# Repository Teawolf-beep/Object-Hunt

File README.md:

# Object-Hunt
Searches and identifies an object in an unknown environment.

This project was developed in the University of Applied Sciences Cologne due to a research project in the subject "Special Aspects of Mobile Autonomous Systems". 

## Documentation

Please refer to the [documentation page](https://teawolf-beep.github.io/index.html) for all further information regarding the project.

## Repository Structure

The following briefly describes the content of the existing directories.

Directory | Content
---|---
Eagle | Circuit schematics and PCB layout. Drafted with [Autodesk EAGLE](https://www.autodesk.com/products/eagle/overview).
Files_rpi | Configuration files of the Raspberry Pi. The exact path is written in the first line of each file.
Final_presentation | A demonstration video and the slides of the final presentation (presentation_team00.pdf).
FreeCAD | Construction files of 3D printed parts. Drafted with [FreeCAD](https://www.freecadweb.org/).
Kick-off_presentation | The slides of the kick-off presentation.
Proposal | The proposal written at the beginning of this project (proposal_group0.pdf).
Report | The final report (report.pdf).
object_hunt_base | Source code of the base process. Written in C++.
object_hunt_camera | Source code of the camera process. Written in Python.
object_hunt_mapping | Source code of the mapping process. Written in Java.
object_hunt_navigation | Source code of the navigation process. Written in C++.
scripts | Bash scripts to facilitate the usage of external software.

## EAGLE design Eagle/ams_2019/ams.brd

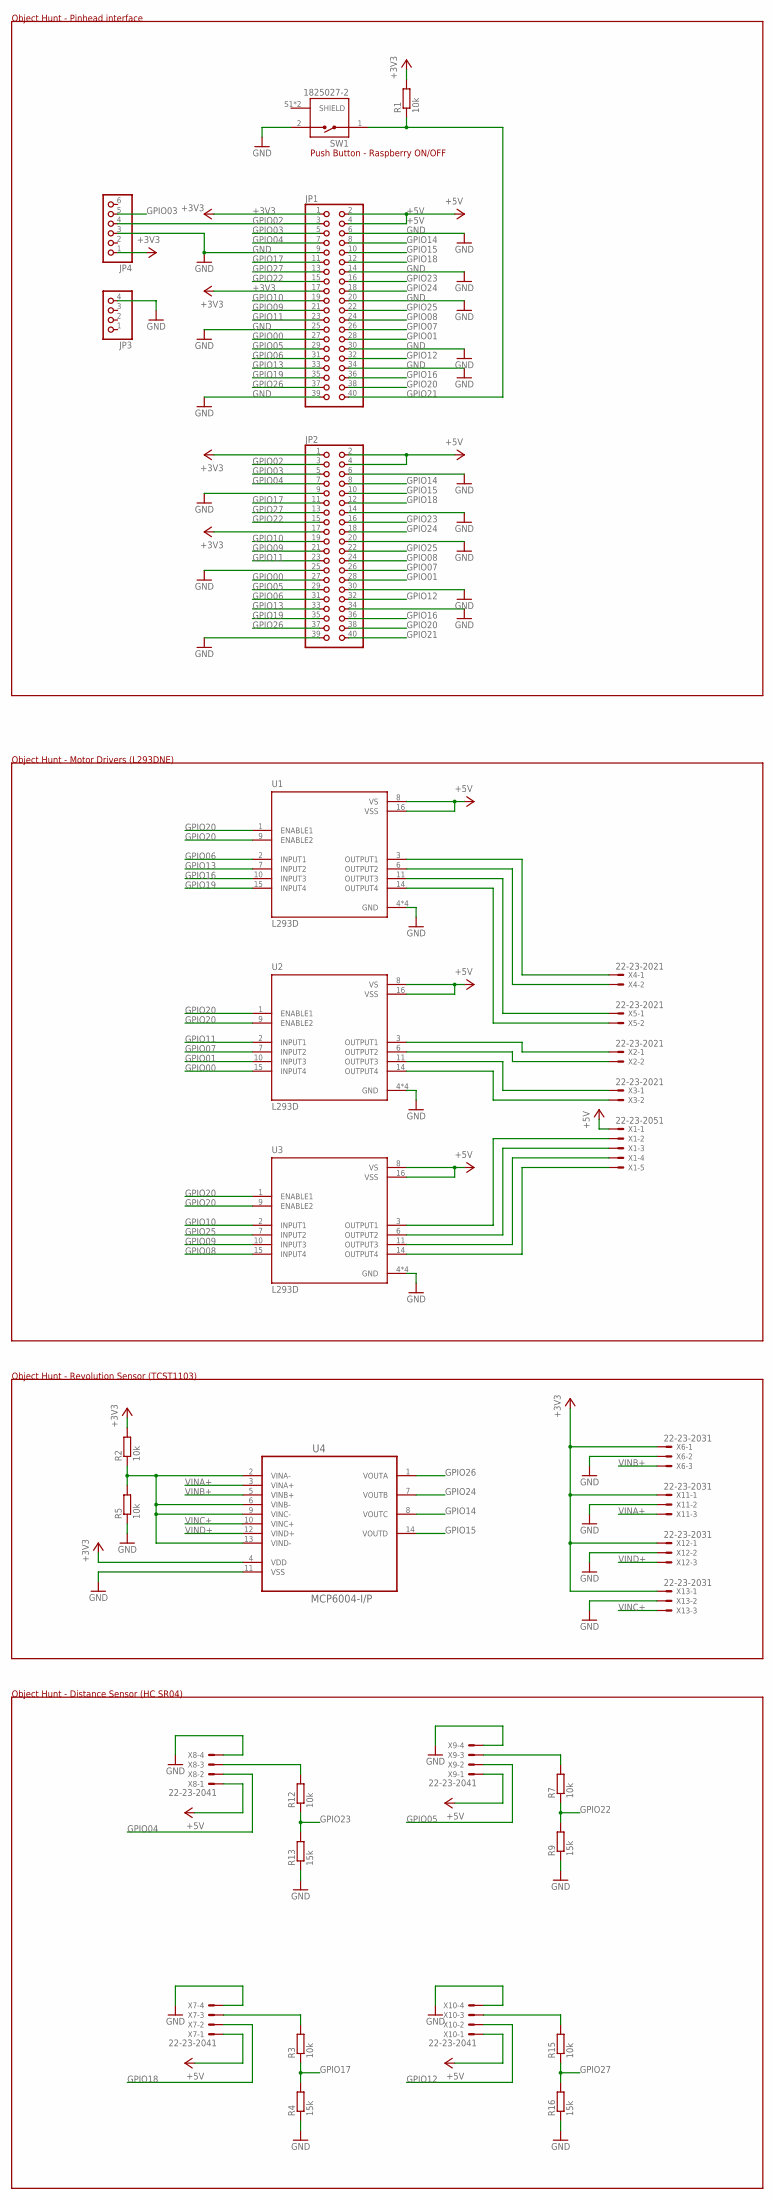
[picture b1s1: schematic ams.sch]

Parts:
JP1, JP2: PINHD-2X20; 2X20
JP3: PINHD-1X4; 1X04
JP4: PINHD-1X6; 1X06
R1, R2, R3, R5, R7, R12, R15: 10k; 0204/7
R4, R9, R13, R16: 15k; 0204/7
SW1: 1825027-2; TE_1825027-2
U1, U2, U3: L293D; DIP880W50P254L2000H510Q16
U4: MCP6004-I/P; DIP254P762X533-14
X1: 22-23-2051
X2, X3, X4, X5: 22-23-2021
X6, X11, X12, X13: 22-23-2031
X7, X8, X9, X10: 22-23-2041

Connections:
+3V3: JP1.1, JP1.17, JP2.1, JP2.17, JP4.1, R1.2, R2.2, U4.4 (VDD), X6.1, X11.1, X12.1, X13.1
+5V: JP1.2, JP1.4, JP2.2, JP2.4, U1.8 (VS), U1.16 (VSS), U2.8 (VS), U2.16 (VSS), U3.8 (VS), U3.16 (VSS), X1.1, X7.1, X8.1, X9.1, X10.1
GND: JP1.6, JP1.9, JP1.14, JP1.20, JP1.25, JP1.30, JP1.34, JP1.39, JP2.6, JP2.9, JP2.14, JP2.20, JP2.25, JP2.30, JP2.34, JP2.39, JP3.4, JP4.3, R4.1, R5.1, R9.1, R13.1, R16.1, SW1.2, U1.4 (GND), U1.5 (GND), U1.12 (GND), U1.13 (GND), U2.4 (GND), U2.5 (GND), U2.12 (GND), U2.13 (GND), U3.4 (GND), U3.5 (GND), U3.12 (GND), U3.13 (GND), U4.11 (VSS), X6.2, X7.4, X8.4, X9.4, X10.4, X11.2, X12.2, X13.2
GPIO00: JP1.27, JP2.27, U2.15 (INPUT4)
GPIO01: JP1.28, JP2.28, U2.10 (INPUT3)
GPIO02: JP1.3, JP2.3, JP4.4
GPIO03: JP1.5, JP2.5, JP4.5
GPIO04: JP1.7, JP2.7, X8.2
GPIO05: JP1.29, JP2.29, X9.2
GPIO06: JP1.31, JP2.31, U1.2 (INPUT1)
GPIO07: JP1.26, JP2.26, U2.7 (INPUT2)
GPIO08: JP1.24, JP2.24, U3.15 (INPUT4)
GPIO09: JP1.21, JP2.21, U3.10 (INPUT3)
GPIO10: JP1.19, JP2.19, U3.2 (INPUT1)
GPIO11: JP1.23, JP2.23, U2.2 (INPUT1)
GPIO12: JP1.32, JP2.32, X10.2
GPIO13: JP1.33, JP2.33, U1.7 (INPUT2)
GPIO14: JP1.8, JP2.8, U4.8 (VOUTC)
GPIO15: JP1.10, JP2.10, U4.14 (VOUTD)
GPIO16: JP1.36, JP2.36, U1.10 (INPUT3)
GPIO17: JP1.11, JP2.11, R3.1, R4.2
GPIO18: JP1.12, JP2.12, X7.2
GPIO19: JP1.35, JP2.35, U1.15 (INPUT4)
GPIO20: JP1.38, JP2.38, U1.1 (ENABLE1), U1.9 (ENABLE2), U2.1 (ENABLE1), U2.9 (ENABLE2), U3.1 (ENABLE1), U3.9 (ENABLE2)
GPIO21: JP1.40, JP2.40, R1.1, SW1.1
GPIO22: JP1.15, JP2.15, R7.1, R9.2
GPIO23: JP1.16, JP2.16, R12.1, R13.2
GPIO24: JP1.18, JP2.18, U4.7 (VOUTB)
GPIO25: JP1.22, JP2.22, U3.7 (INPUT2)
GPIO26: JP1.37, JP2.37, U4.1 (VOUTA)
GPIO27: JP1.13, JP2.13, R15.1, R16.2
unnamed: R3.2, X7.3
unnamed: R2.1, R5.2, U4.2 (VINA-), U4.6 (VINB-), U4.9 (VINC-), U4.13 (VIND-)
unnamed: R7.2, X9.3
unnamed: R15.2, X10.3
unnamed: U1.3 (OUTPUT1), X4.1
unnamed: U1.6 (OUTPUT2), X4.2
unnamed: U1.11 (OUTPUT3), X5.1
unnamed: U1.14 (OUTPUT4), X5.2
unnamed: U2.3 (OUTPUT1), X2.1
unnamed: U2.6 (OUTPUT2), X2.2
unnamed: U2.11 (OUTPUT3), X3.1
unnamed: U2.14 (OUTPUT4), X3.2
unnamed: U3.3 (OUTPUT1), X1.2
unnamed: U3.6 (OUTPUT2), X1.3
unnamed: U3.11 (OUTPUT3), X1.4
unnamed: U3.14 (OUTPUT4), X1.5
unnamed: R12.2, X8.3
VINA+: U4.3 (VINA+), X11.3
VINB+: U4.5 (VINB+), X6.3
VINC+: U4.10 (VINC+), X13.3
VIND+: U4.12 (VIND+), X12.3

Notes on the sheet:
Push Button - Raspberry ON/OFF
Object Hunt - Pinhead interface
Object Hunt - Distance Sensor (HC SR04)
Object Hunt - Revolution Sensor (TCST1103)
Object Hunt - Motor Drivers (L293DNE)

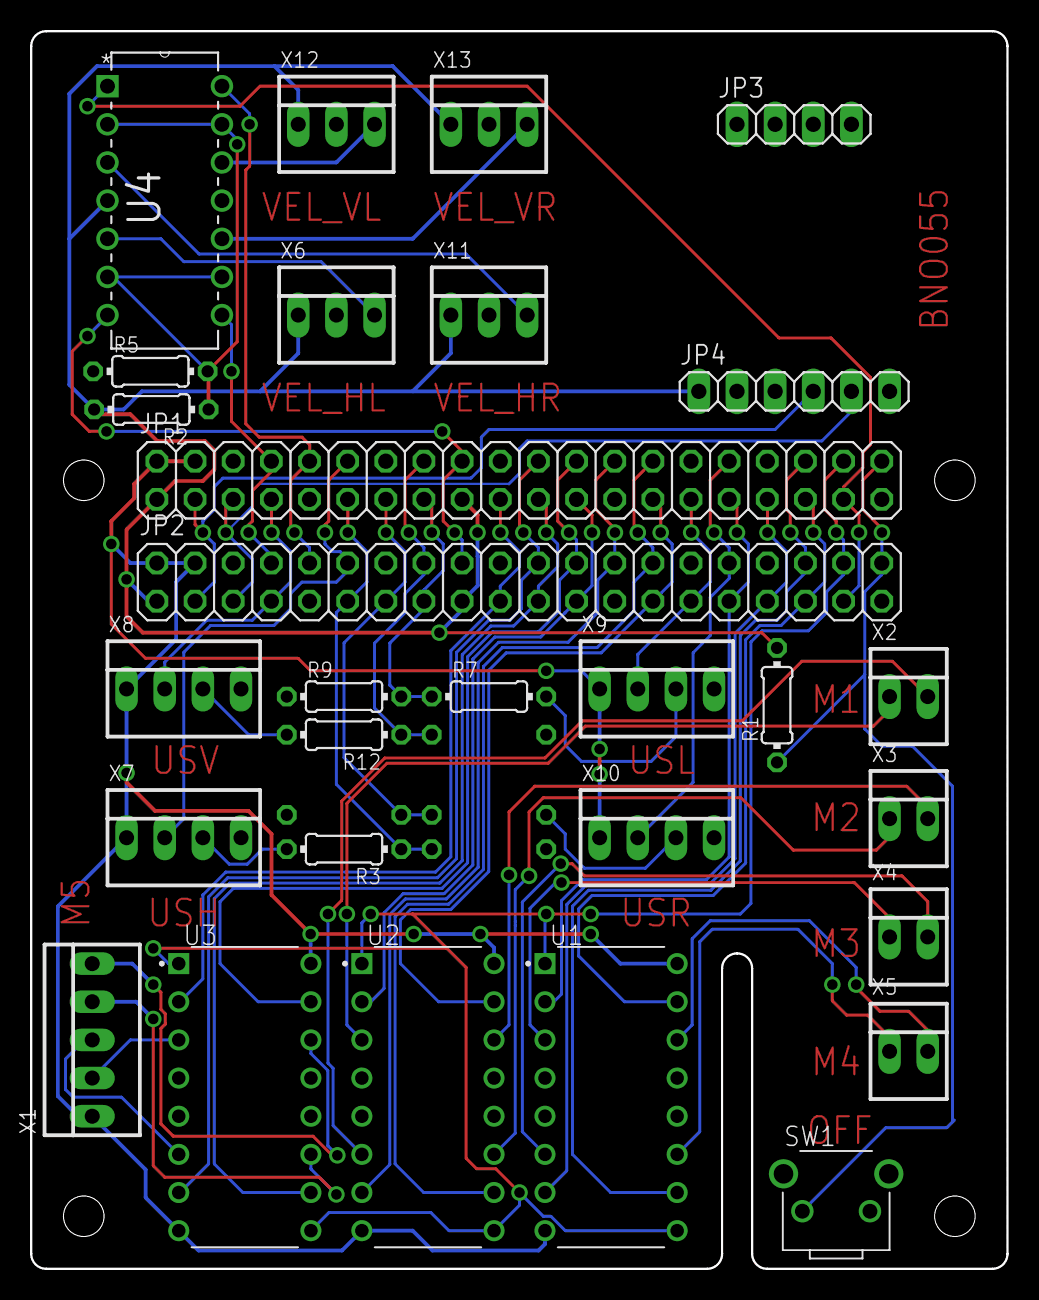
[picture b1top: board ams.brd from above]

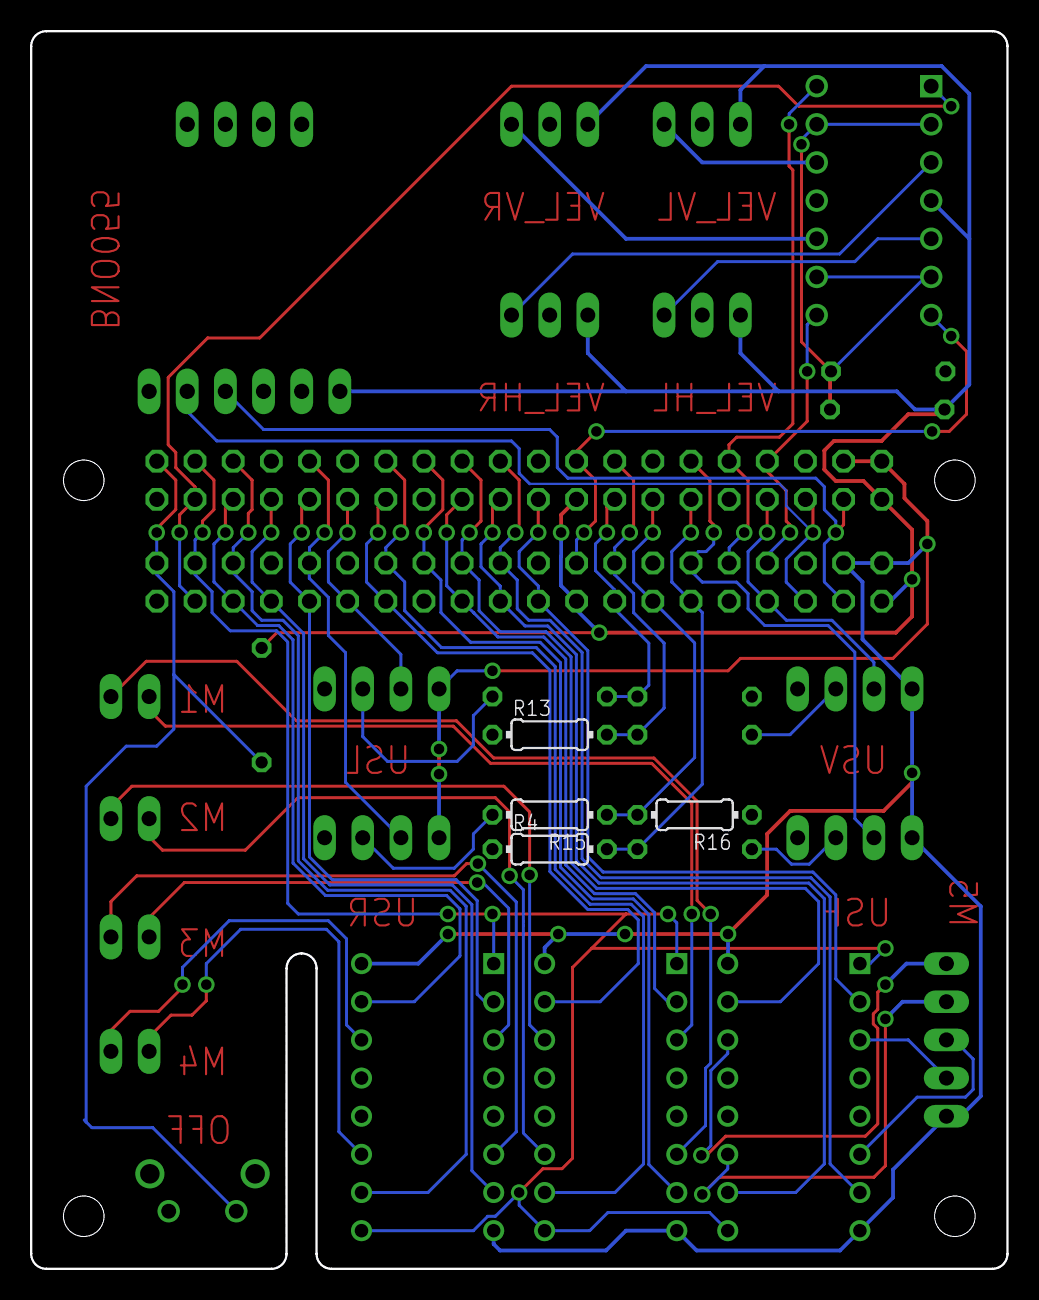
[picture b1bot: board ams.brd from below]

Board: 2 copper layers, 65.0 x 82.4 mm, 33 parts (4 on the bottom side), 52 nets.

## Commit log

2020-01-30 README.md updated
2020-01-30 Report updated
2020-01-31 Mapping folder oganized
2020-02-01 Report updated (added mapping part)
2020-02-02 Create part_image_processing
2020-02-02 Add files via upload
    report part for image processing
2020-02-02 Include image processing in report
2020-02-02 Update image processing in report
2020-02-05 Report complete
2020-02-05 Report completed
2020-02-05 Video on main page
2020-02-15 Removed comment on mapping part
